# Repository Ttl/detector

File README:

1 MHz - 10 GHz RF power detector with USB connection.

Based on AD8319 power detector and LPC11U68 microcontroller.

Hardware:

hardware: KiCad files of the board.

Firmware:

lpc_chip_11u6x
lpc_board_detector
detector

Compile with LPCXpresso IDE.

Software:

detector.py: Main code.

ad8139cal.py: Voltage to dBm calibration table.

scalar_vna.py: Scalar network analyzer using two power sensors, two directional couplers and VNA as a signal source. VNA code can be got from: https://github.com/Ttl/vna.

analysis.py: Reflection tracking calibration and plotting the results of scalar network analyzer measurements.

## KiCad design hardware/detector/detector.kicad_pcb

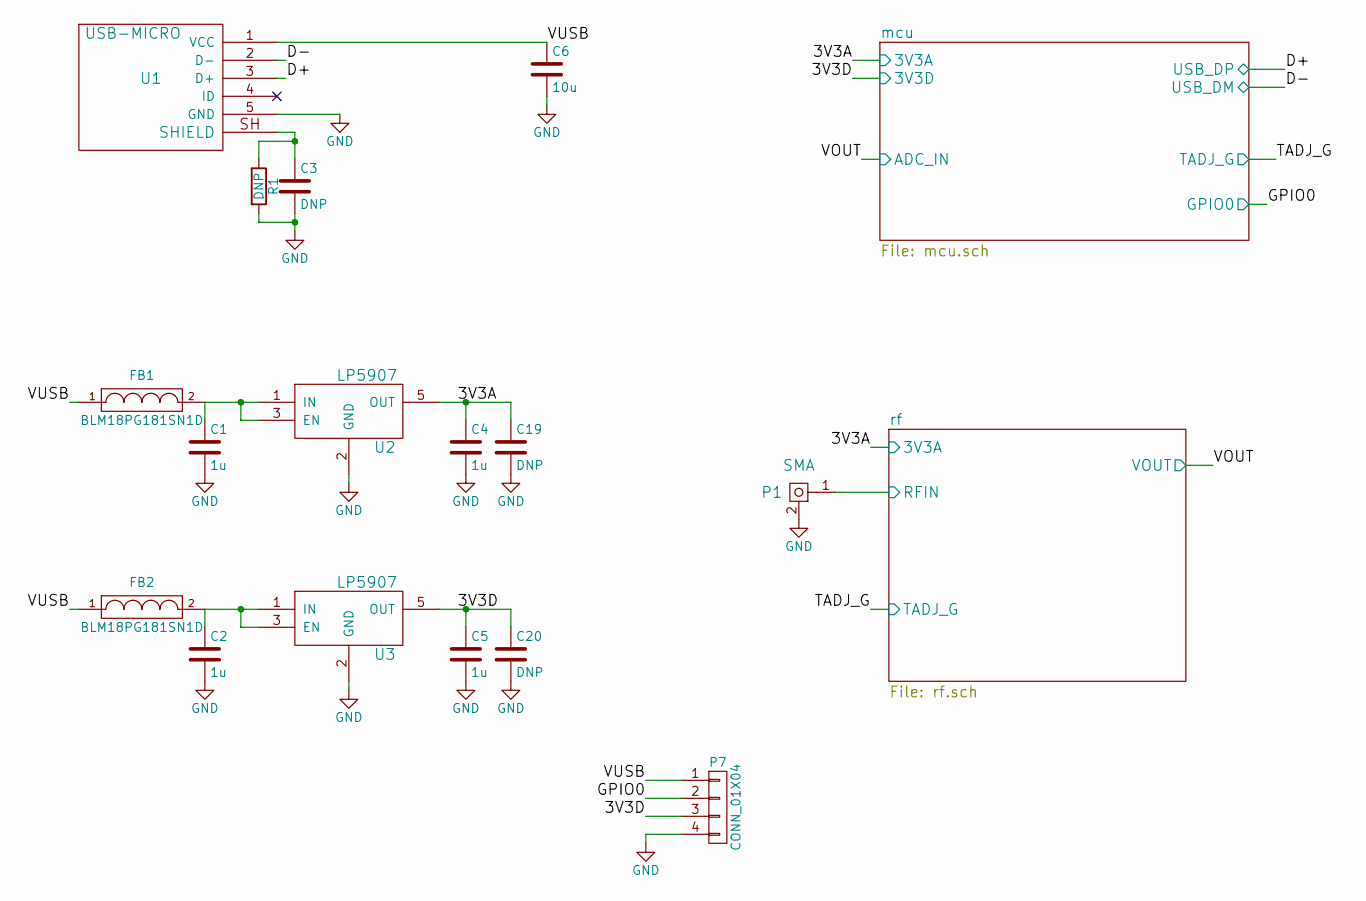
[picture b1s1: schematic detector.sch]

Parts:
C1, C2, C4, C5: 1u; C_0603b
C3: DNP; C_0402b
C6: 10u; C_0805b
C19, C20: DNP; C_0805b
FB1, FB2: BLM18PG181SN1D; C_0603b
P1: SMA; CONSMA003.062
P7: CONN_01X04; Pin_Header_Straight_1x04
R1: DNP; R_0402b
U1: USB-MICRO; USB_MICRO
U2, U3: LP5907; SOT-23-5

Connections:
/3V3A: C4.1, C19.1, U2.5 (OUT); also elsewhere on the board
/3V3D: C5.1, C20.1, P7.3, U3.5 (OUT); also elsewhere on the board
/D+: U1.3 (D+); also elsewhere on the board
/D-: U1.2 (D-); also elsewhere on the board
/GPIO0: P7.2; also elsewhere on the board
/VUSB: C6.1, FB1.1, FB2.1, P7.1, U1.1 (VCC)
/rf/RFIN: P1.1; also elsewhere on the board
GND: C1.2, C2.2, C3.2, C4.2, C5.2, C6.2, C19.2, C20.2, P1.2, P7.4, R1.2, U1.5 (GND), U2.2 (GND), U3.2 (GND); also elsewhere on the board
unnamed: C1.1, FB1.2, U2.1 (IN), U2.3 (EN)
unnamed: C2.1, FB2.2, U3.1 (IN), U3.3 (EN)
unnamed: C3.1, R1.1, U1.SH (SHIELD)

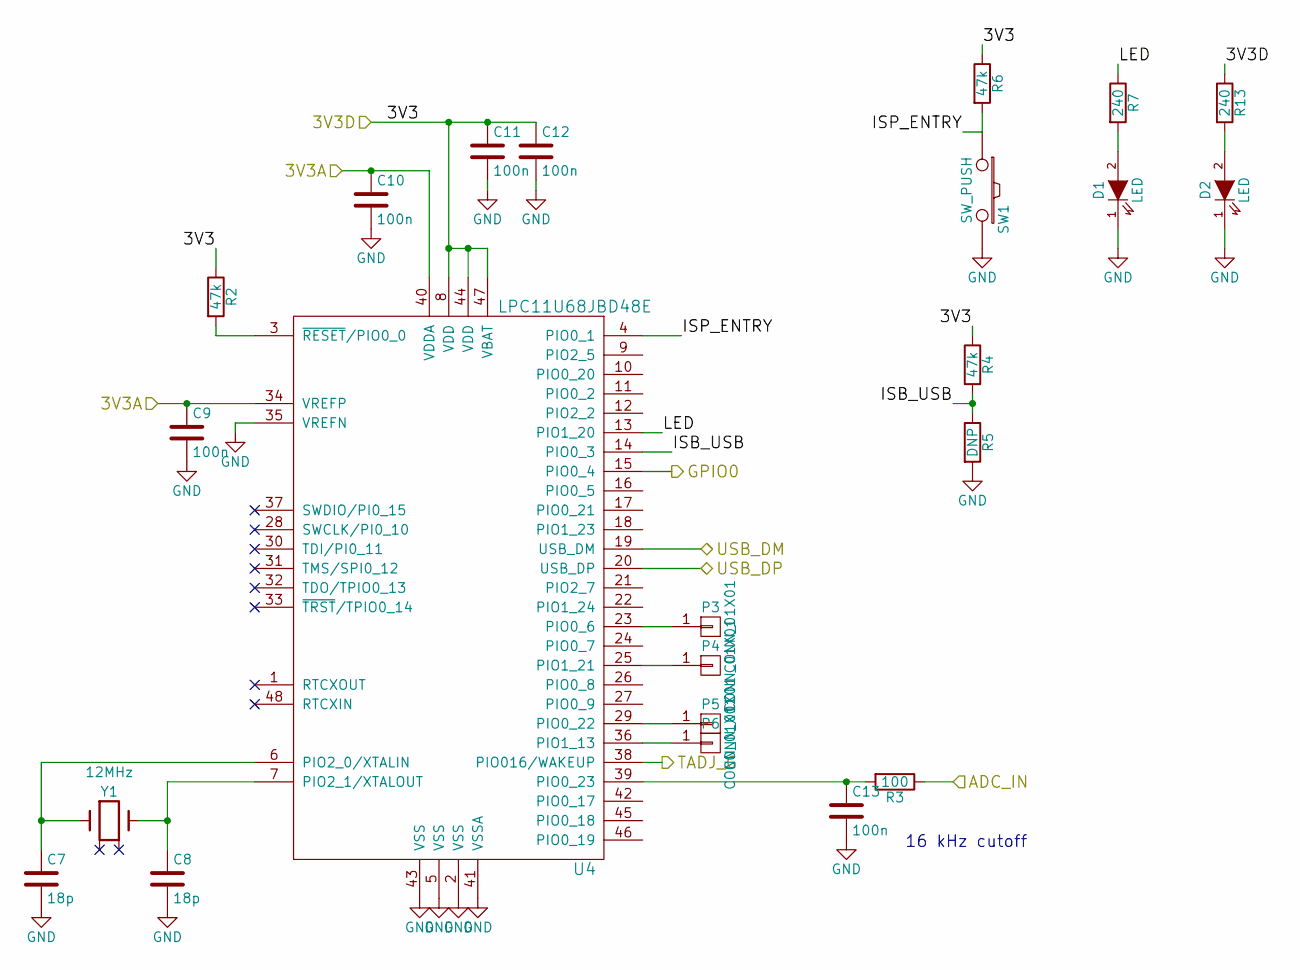
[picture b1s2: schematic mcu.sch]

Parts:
C7, C8: 18p; C_0402b
C9, C10, C11, C12, C13: 100n; C_0402b
D1, D2: LED; LED_0603
P3, P4, P5, P6: CONN_01X01; TP_1.00
R2, R4, R6: 47k; R_0402b
R3: 100; R_0402b
R5: DNP; R_0402b
R7, R13: 240; R_0402b
SW1: SW_PUSH; EVP-AWBA2A
U4: LPC11U68JBD48E; LQFP-48_7x7mm_Pitch0.5mm
Y1: 12MHz; XTAL_3.2x2.5

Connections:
/3V3A: C9.1, C10.1, U4.34 (VREFP), U4.40 (VDDA); also elsewhere on the board
/3V3D: C11.1, C12.1, R2.1, R4.1, R6.1, R13.1, U4.8 (VDD), U4.44 (VDD), U4.47 (VBAT); also elsewhere on the board
/D+: U4.20 (USB_DP); also elsewhere on the board
/D-: U4.19 (USB_DM); also elsewhere on the board
/GPIO0: U4.15 (PIO0_4); also elsewhere on the board
/TADJ_G: U4.38 (PIO016/WAKEUP); also elsewhere on the board
/VOUT: R3.1; also elsewhere on the board
/mcu/ISB_USB: R4.2, R5.1, U4.14 (PIO0_3)
/mcu/ISP_ENTRY: R6.2, SW1.1, U4.4 (PIO0_1)
/mcu/LED: R7.1, U4.13 (PIO1_20)
GND: C7.2, C8.2, C9.2, C10.2, C11.2, C12.2, C13.2, D1.1 (K), D2.1 (K), R5.2, SW1.2, U4.2 (VSS), U4.5 (VSS), U4.35 (VREFN), U4.41 (VSSA), U4.43 (VSS); also elsewhere on the board
unnamed: C7.1, U4.6 (PIO2_0/XTALIN), Y1.1
unnamed: C8.1, U4.7 (PIO2_1/XTALOUT), Y1.3
unnamed: C13.1, R3.2, U4.39 (PIO0_23)
unnamed: D1.2 (A), R7.2
unnamed: D2.2 (A), R13.2
unnamed: P3.1, U4.23 (PIO0_6)
unnamed: P4.1, U4.25 (PIO1_21)
unnamed: P5.1, U4.29 (PIO0_22)
unnamed: P6.1, U4.36 (PIO1_13)
unnamed: R2.2, U4.3 (~RESET~/PIO0_0)

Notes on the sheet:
16 kHz cutoff

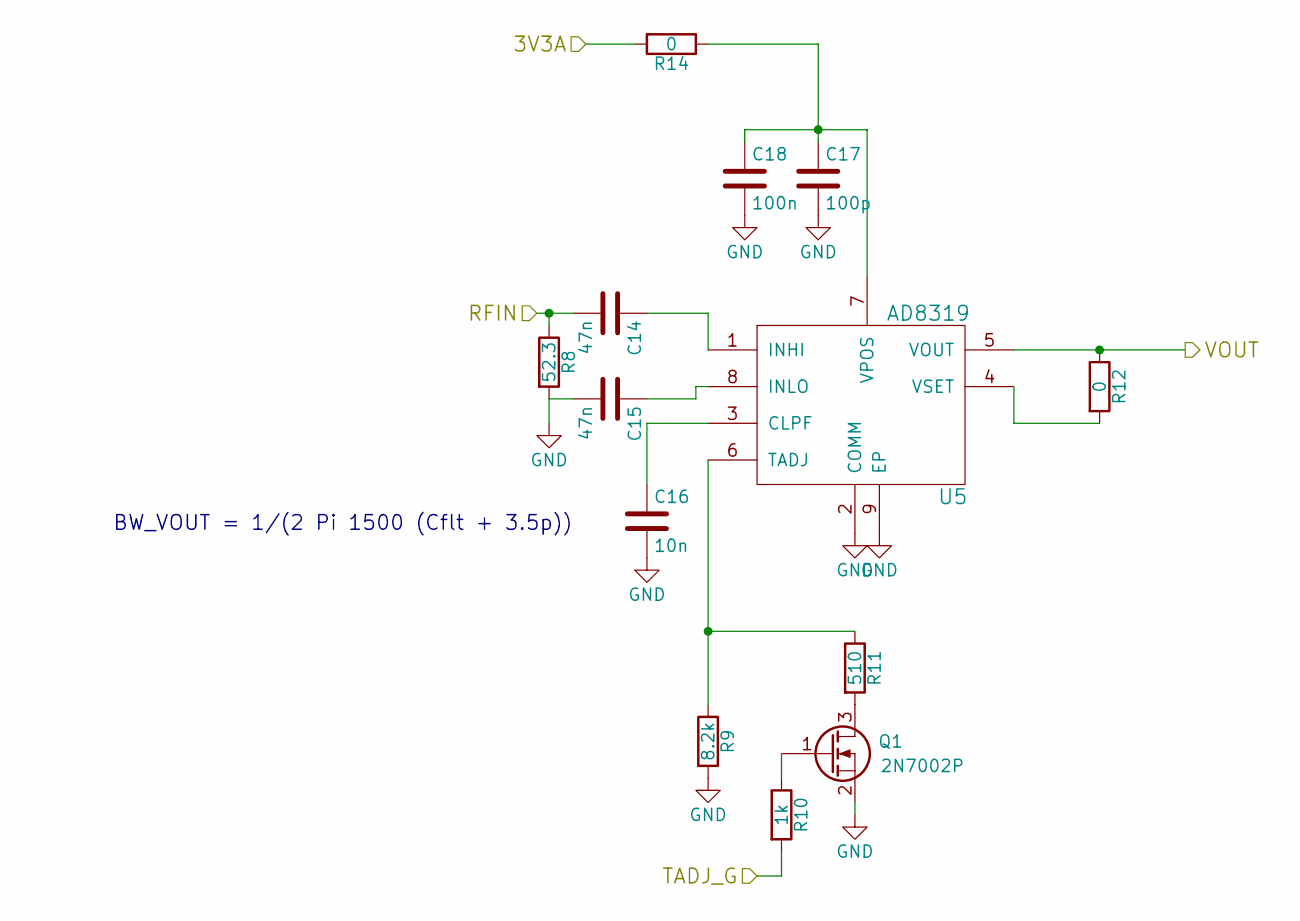
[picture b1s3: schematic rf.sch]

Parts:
C14, C15: 47n; C_0402b
C16: 10n; C_0402b
C17: 100p; C_0402b
C18: 100n; C_0402b
Q1: 2N7002P; SOT-23
R8: 52.3; R_0402b
R9: 8.2k; R_0402b
R10: 1k; R_0402b
R11: 510; R_0402b
R12, R14: 0; R_0402b
U5: AD8319; LFCSP-8

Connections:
/3V3A: R14.2; also elsewhere on the board
/TADJ_G: R10.2; also elsewhere on the board
/VOUT: R12.1, U5.5 (VOUT); also elsewhere on the board
/rf/RFIN: C14.2, R8.1; also elsewhere on the board
GND: C15.2, C16.2, C17.2, C18.2, Q1.2 (S), R8.2, R9.2, U5.2 (COMM), U5.9 (EP); also elsewhere on the board
unnamed: C14.1, U5.1 (INHI)
unnamed: C15.1, U5.8 (INLO)
unnamed: C16.1, U5.3 (CLPF)
unnamed: C17.1, C18.1, R14.1, U5.7 (VPOS)
unnamed: Q1.1 (G), R10.1
unnamed: Q1.3 (D), R11.2
unnamed: R9.1, R11.1, U5.6 (TADJ)
unnamed: R12.2, U5.4 (VSET)

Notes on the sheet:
BW_VOUT = 1/(2 Pi 1500 (Cflt + 3.5p))

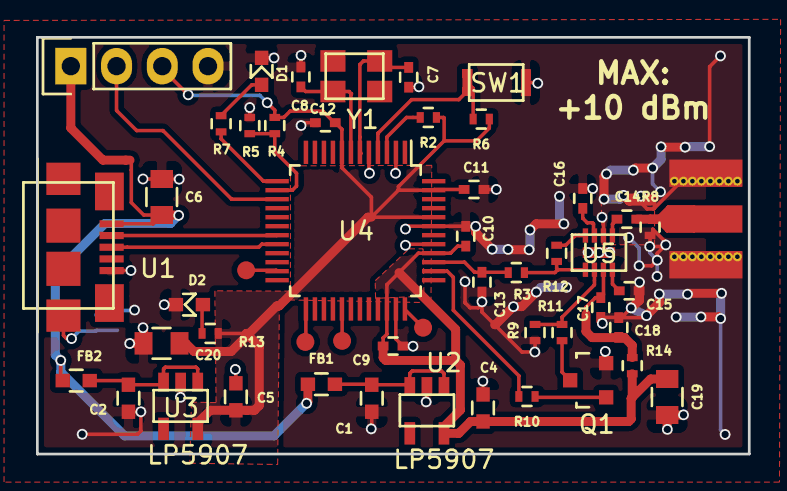
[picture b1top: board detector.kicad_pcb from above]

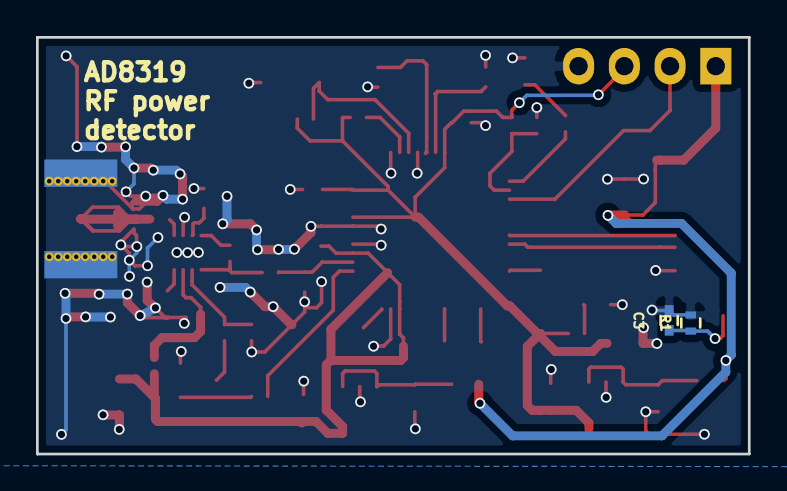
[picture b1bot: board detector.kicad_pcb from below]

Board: 2 copper layers, 39.5 x 23.2 mm, 52 parts (2 on the bottom side), 34 nets.

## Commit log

2016-10-25 Remove debug code
